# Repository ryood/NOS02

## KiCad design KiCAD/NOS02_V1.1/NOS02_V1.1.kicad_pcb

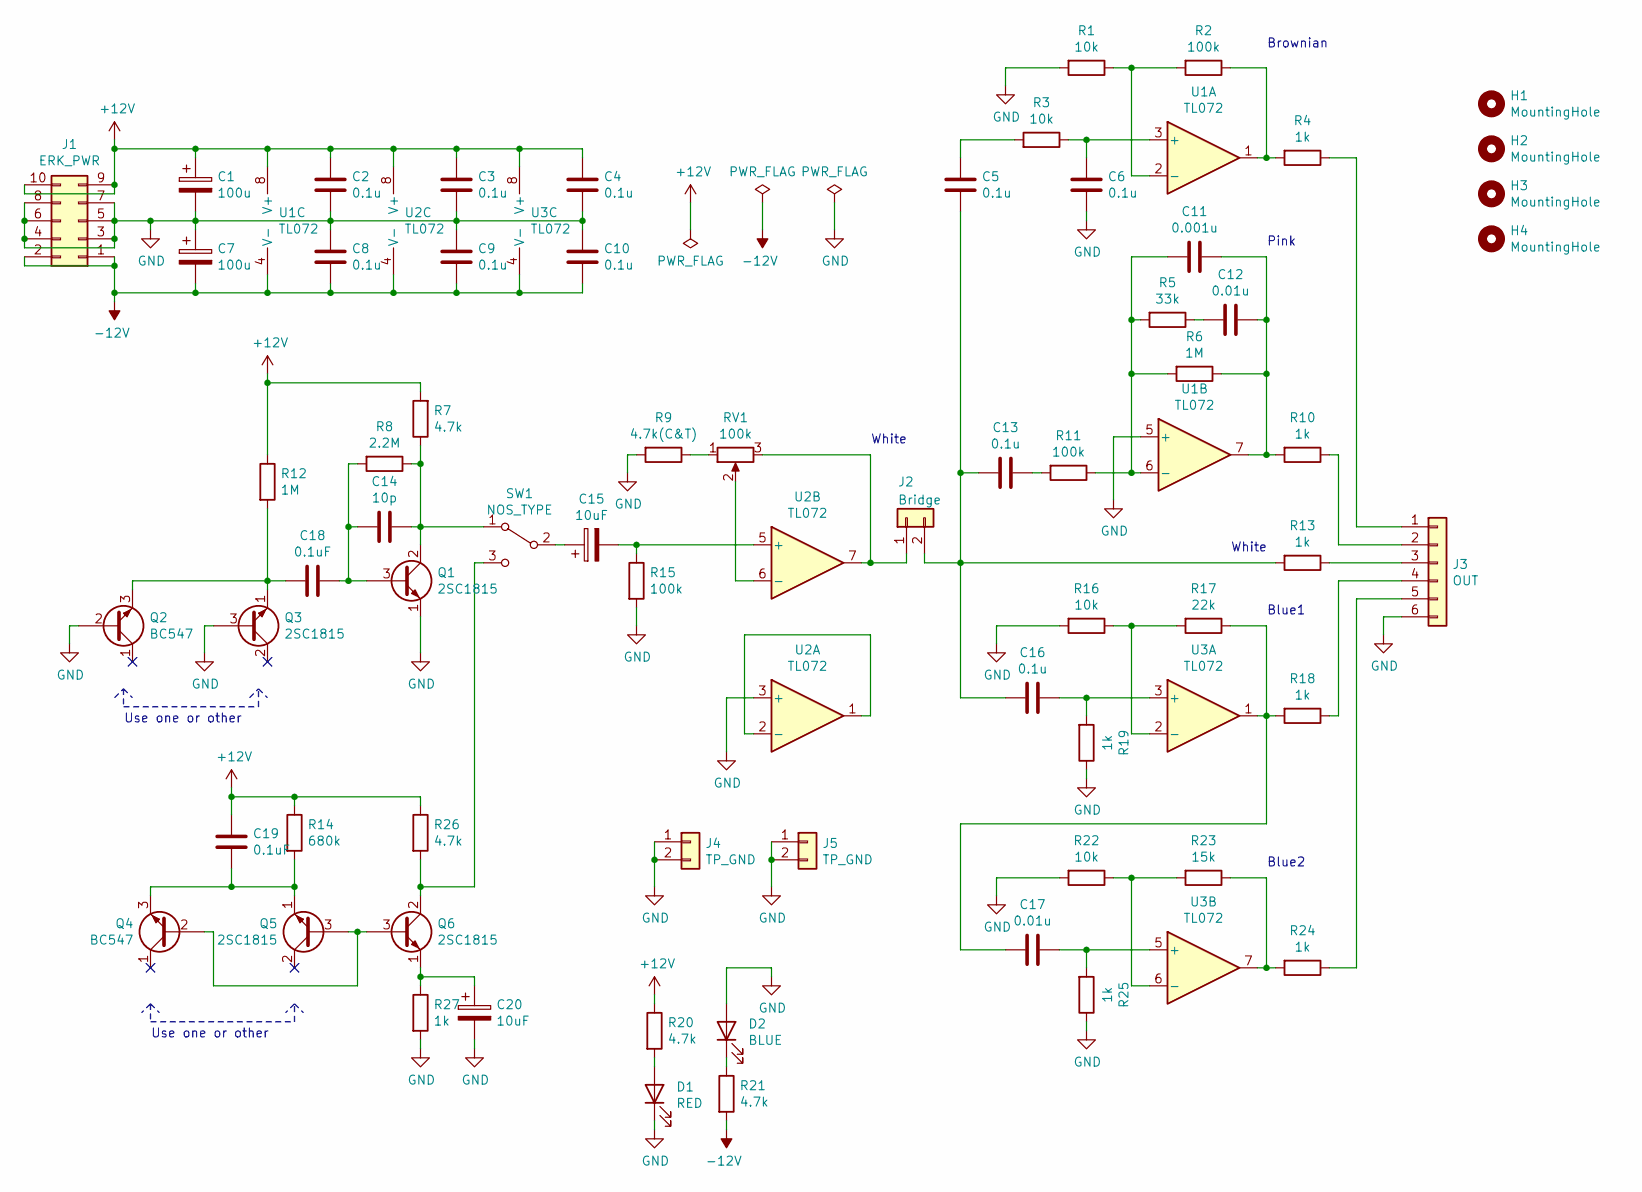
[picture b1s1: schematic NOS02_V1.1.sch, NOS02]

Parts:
C1, C7: 100u; CP_Radial_D6.3mm_P2.50mm
C2, C3, C4, C8, C9, C10: 0.1u; C_Disc_D3.0mm_W1.6mm_P2.50mm
C5, C6, C13, C16: 0.1u; C_Rect_L7.2mm_W3.0mm_P5.00mm_FKS2_FKP2_MKS2_MKP2
C11: 0.001u; C_Rect_L7.2mm_W3.0mm_P5.00mm_FKS2_FKP2_MKS2_MKP2
C12, C17: 0.01u; C_Rect_L7.2mm_W3.0mm_P5.00mm_FKS2_FKP2_MKS2_MKP2
C14: 10p; C_Disc_D3.0mm_W2.0mm_P2.50mm
C15, C20: 10uF; CP_Radial_D5.0mm_P2.50mm
C18, C19: 0.1uF; C_Rect_L7.2mm_W3.0mm_P5.00mm_FKS2_FKP2_MKS2_MKP2
D1: RED; LED_D3.0mm
D2: BLUE; LED_D3.0mm
H1, H2, H3, H4: MountingHole; MountingHole_3.2mm_M3
J1: ERK_PWR; IDC-Header_2x05_P2.54mm_Vertical
J2: Bridge; PinHeader_1x02_P2.54mm_Vertical
J3: OUT; JST_XH_B6B-XH-A_1x06_P2.50mm_Vertical
J4, J5: TP_GND; PinHeader_1x02_P2.54mm_Vertical
Q1, Q3, Q5, Q6: 2SC1815; TO-92_Inline_Wide
Q2, Q4: BC547; TO-92_Inline_Wide
R1, R3, R16, R22: 10k; R_Axial_DIN0207_L6.3mm_D2.5mm_P10.16mm_Horizontal
R2, R11, R15: 100k; R_Axial_DIN0207_L6.3mm_D2.5mm_P10.16mm_Horizontal
R4, R10, R13, R18, R19, R24, R25, R27: 1k; R_Axial_DIN0207_L6.3mm_D2.5mm_P10.16mm_Horizontal
R5: 33k; R_Axial_DIN0207_L6.3mm_D2.5mm_P10.16mm_Horizontal
R6, R12: 1M; R_Axial_DIN0207_L6.3mm_D2.5mm_P10.16mm_Horizontal
R7, R20, R21, R26: 4.7k; R_Axial_DIN0207_L6.3mm_D2.5mm_P10.16mm_Horizontal
R8: 2.2M; R_Axial_DIN0207_L6.3mm_D2.5mm_P10.16mm_Horizontal
R9: 4.7k(C&T); R_Axial_DIN0207_L6.3mm_D2.5mm_P10.16mm_Horizontal
R14: 680k; R_Axial_DIN0207_L6.3mm_D2.5mm_P10.16mm_Horizontal
R17: 22k; R_Axial_DIN0207_L6.3mm_D2.5mm_P10.16mm_Horizontal
R23: 15k; R_Axial_DIN0207_L6.3mm_D2.5mm_P10.16mm_Horizontal
RV1: 100k; Potentiometer_Bourns_3362P_Vertical
SW1: NOS_TYPE; JST_XH_B3B-XH-A_1x03_P2.50mm_Vertical
U1, U2, U3: TL072; DIP-8_W7.62mm_Socket

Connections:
+12V: C1.1, C2.2, C3.2, C4.2, C19.2, J1.9, J1.10, R7.2, R12.1, R14.1, R20.1, R26.1, U1.8 (V+), U2.8 (V+), U3.8 (V+)
-12V: C7.2, C8.1, C9.1, C10.1, J1.1, J1.2, R21.2, U1.4 (V-), U2.4 (V-), U3.4 (V-)
GND: C1.2, C2.1, C3.1, C4.1, C6.1, C7.1, C8.2, C9.2, C10.2, C20.2, D1.1 (K), D2.2 (A), J1.3, J1.4, J1.5, J1.6, J1.7, J1.8, J3.6, J4.1, J4.2, J5.1, J5.2, Q1.1 (E), Q2.2 (B), Q3.3 (B), R1.2, R9.2, R15.2, R16.2, R19.1, R22.2, R25.1, R27.2, U1.5 (+), U2.3 (+)
unnamed: C5.2, R3.2
unnamed: C6.2, R3.1, U1.3 (+)
unnamed: C11.1, C12.1, R6.1, R10.2, U1.7
unnamed: C11.2, R5.2, R6.2, R11.1, U1.6 (-)
unnamed: C12.2, R5.1
unnamed: C13.1, R11.2
unnamed: C5.1, C13.2, C16.2, J2.2, R13.2
unnamed: C14.1, Q1.2 (C), R7.1, R8.1, SW1.1 (A)
unnamed: C14.2, C18.1, Q1.3 (B), R8.2
unnamed: C15.1, SW1.2 (B)
unnamed: C15.2, R15.1, U2.5 (+)
unnamed: C16.1, R19.2, U3.3 (+)
unnamed: C17.1, R25.2, U3.5 (+)
unnamed: C17.2, R17.1, R18.2, U3.1
unnamed: C18.2, Q2.3 (E), Q3.1 (E), R12.2
unnamed: C19.1, Q4.3 (E), Q5.1 (E), R14.2
unnamed: C20.1, Q6.1 (E), R27.1
unnamed: D1.2 (A), R20.2
unnamed: D2.1 (K), R21.1
unnamed: J2.1, RV1.3, U2.7
unnamed: J3.1, R4.1
unnamed: J3.2, R10.1
unnamed: J3.3, R13.1
unnamed: J3.4, R18.1
unnamed: J3.5, R24.1
unnamed: Q4.2 (B), Q5.3 (B), Q6.3 (B)
unnamed: Q6.2 (C), R26.2, SW1.3 (C)
unnamed: R1.1, R2.2, U1.2 (-)
unnamed: R2.1, R4.2, U1.1
unnamed: R9.1, RV1.1
unnamed: R16.1, R17.2, U3.2 (-)
unnamed: R22.1, R23.2, U3.6 (-)
unnamed: R23.1, R24.2, U3.7
unnamed: RV1.2, U2.6 (-)
unnamed: U2.1, U2.2 (-)

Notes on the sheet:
Brownian
Pink
Blue1
Blue2
White
Use one or other

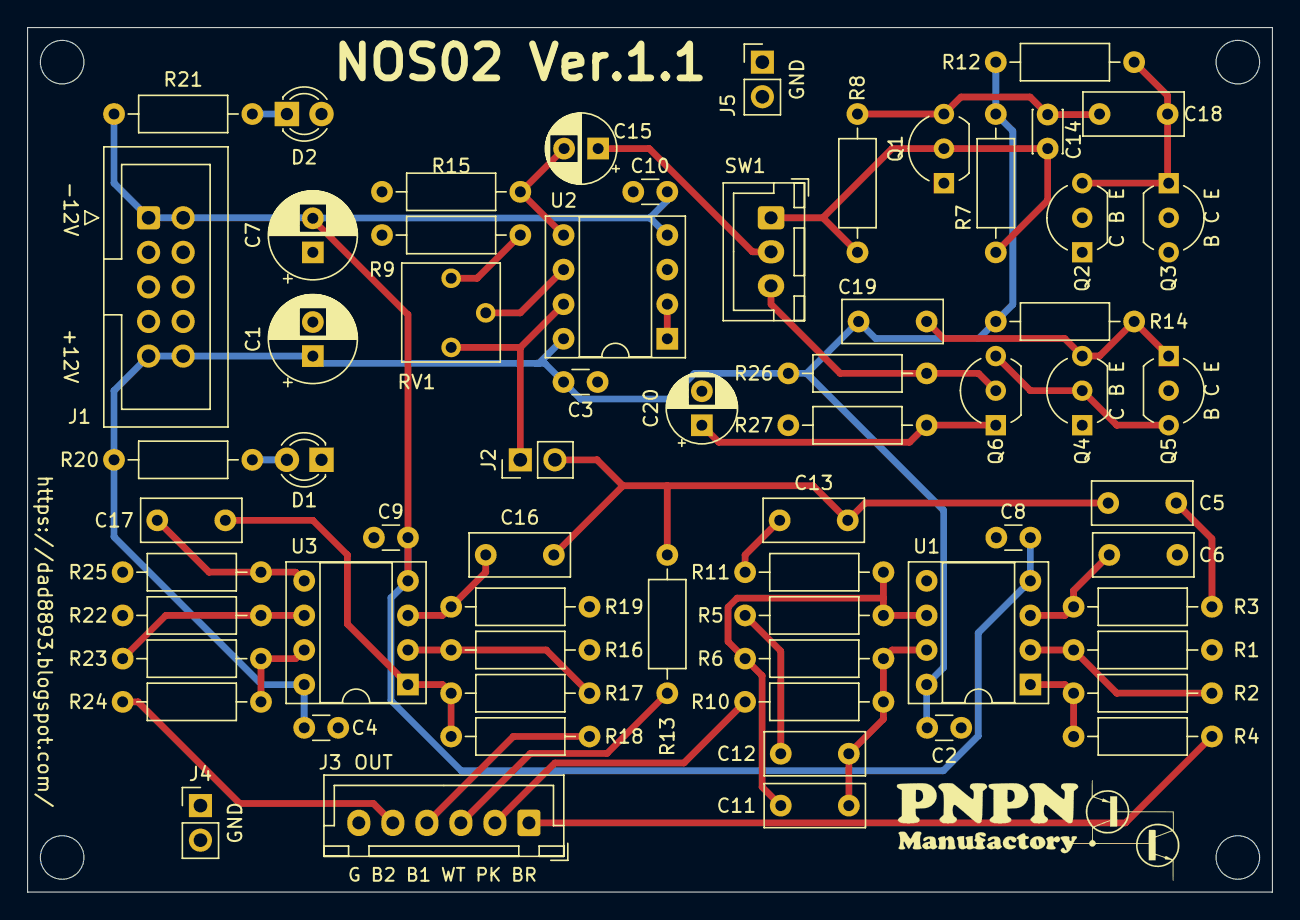
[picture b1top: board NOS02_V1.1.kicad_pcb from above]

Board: 2 copper layers, 91.4 x 63.5 mm, 69 parts (0 on the bottom side), 38 nets.

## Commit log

2021-08-14 Gerber
2021-11-21 Mount
2022-04-13 Ver.1.1
2022-04-14 Blog
